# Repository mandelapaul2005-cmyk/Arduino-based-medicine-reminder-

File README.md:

# Arduino-based-medicine-reminder-
Remind user to take medication 

## Colaborators
1. Masika - Supervisor

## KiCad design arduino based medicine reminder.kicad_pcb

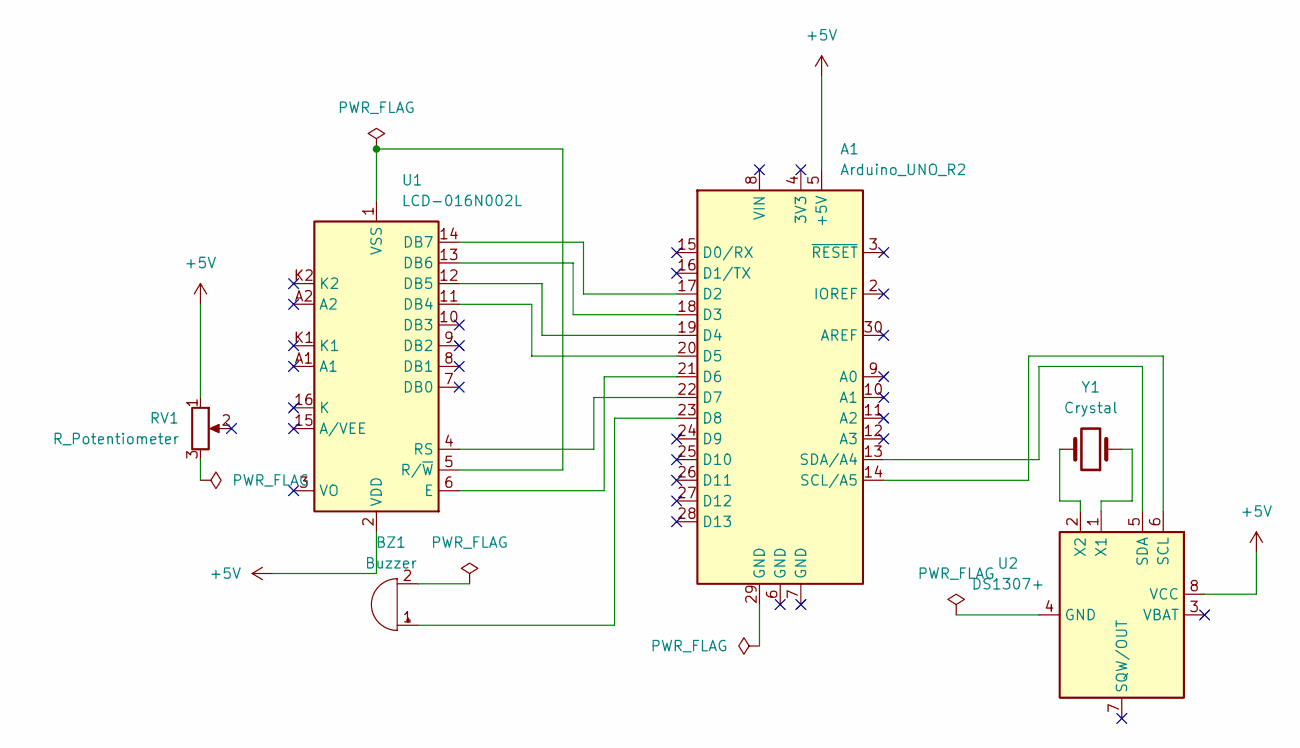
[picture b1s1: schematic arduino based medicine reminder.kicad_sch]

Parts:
A1: Arduino_UNO_R2
BZ1: Buzzer
RV1: R_Potentiometer
U1: LCD-016N002L
U2: DS1307+; DIP-8_W7.62mm
Y1: Crystal

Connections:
+5V: A1.5 (+5V), RV1.1, U1.2 (VDD), U2.8 (VCC)
unnamed: A1.17 (D2), U1.14 (DB7)
unnamed: A1.18 (D3), U1.13 (DB6)
unnamed: A1.19 (D4), U1.12 (DB5)
unnamed: A1.20 (D5), U1.11 (DB4)
unnamed: A1.21 (D6), U1.6 (E)
unnamed: A1.22 (D7), U1.4 (RS)
unnamed: A1.23 (D8), BZ1.1 (+)
unnamed: A1.14 (SCL/A5), U2.6 (SCL)
unnamed: A1.13 (SDA/A4), U2.5 (SDA)
unnamed: U1.1 (VSS), U1.5 (R/~W)
unnamed: U2.1 (X1), Y1.1
unnamed: U2.2 (X2), Y1.2

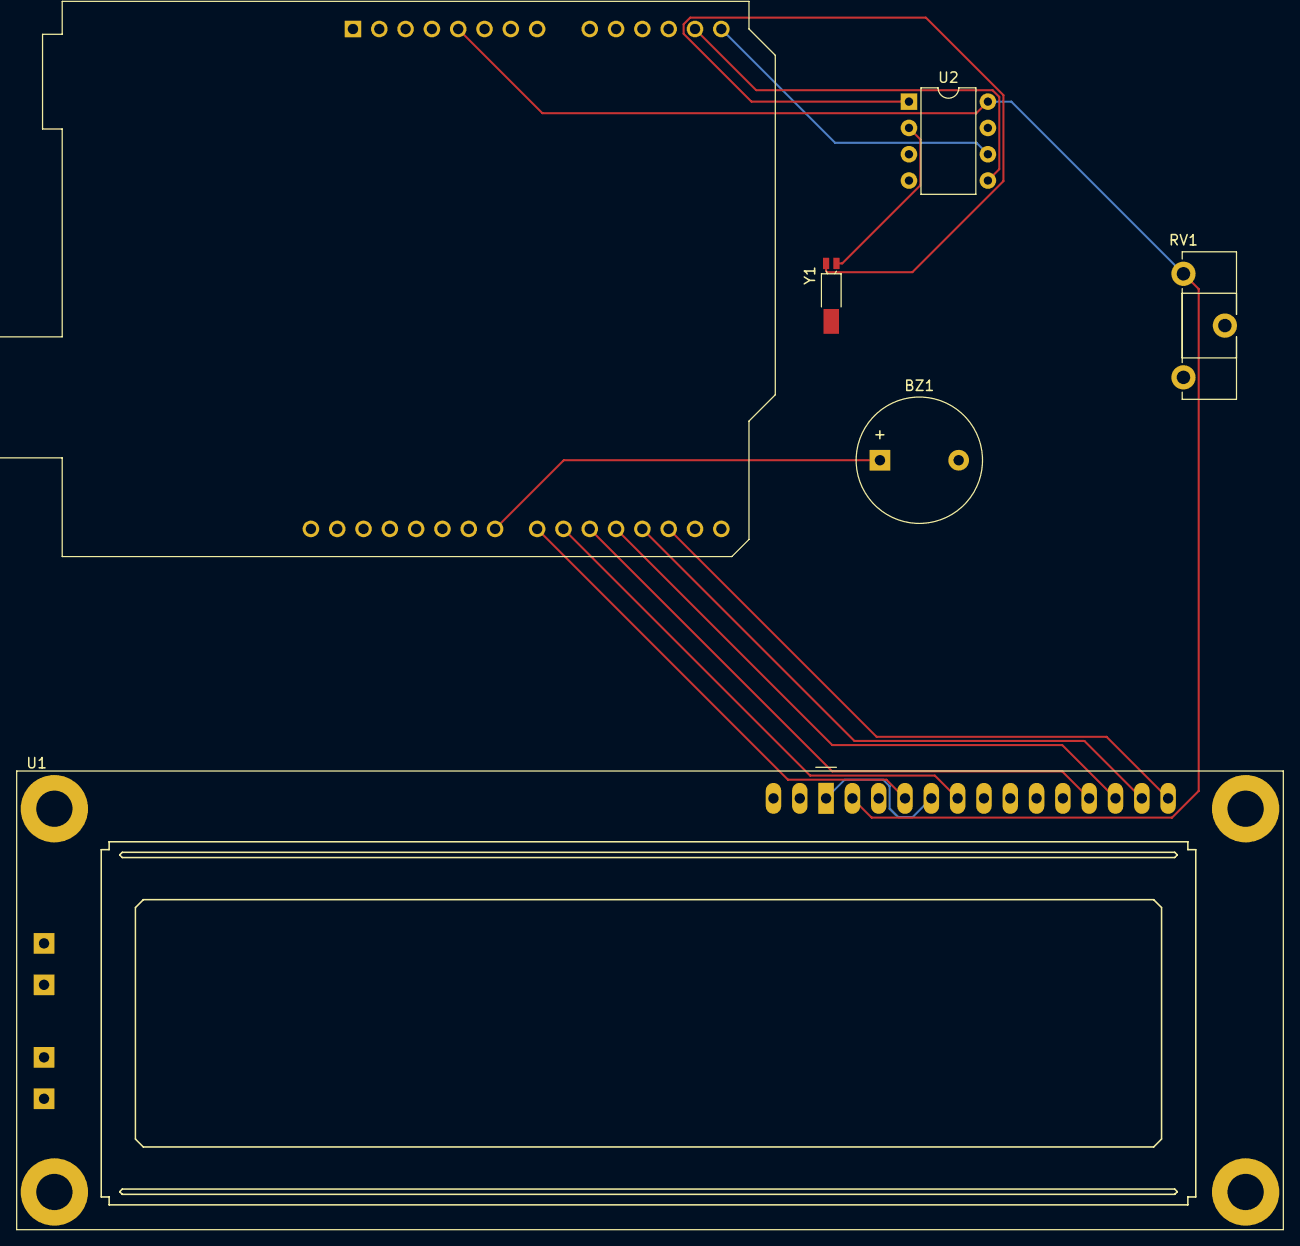
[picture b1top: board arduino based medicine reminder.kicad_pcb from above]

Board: 2 copper layers, 6 parts (0 on the bottom side), 13 nets.
